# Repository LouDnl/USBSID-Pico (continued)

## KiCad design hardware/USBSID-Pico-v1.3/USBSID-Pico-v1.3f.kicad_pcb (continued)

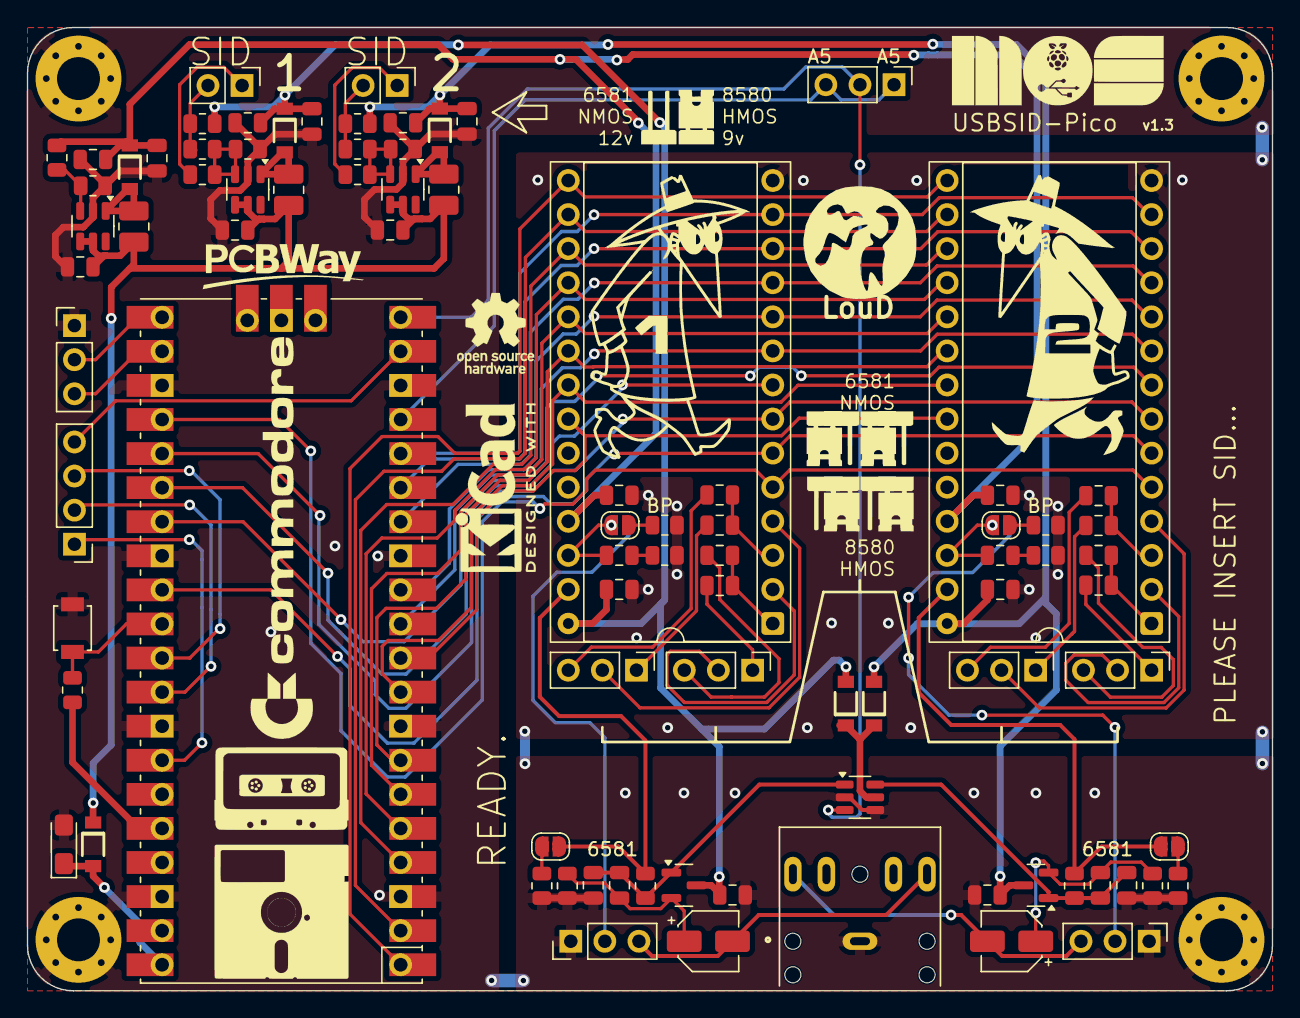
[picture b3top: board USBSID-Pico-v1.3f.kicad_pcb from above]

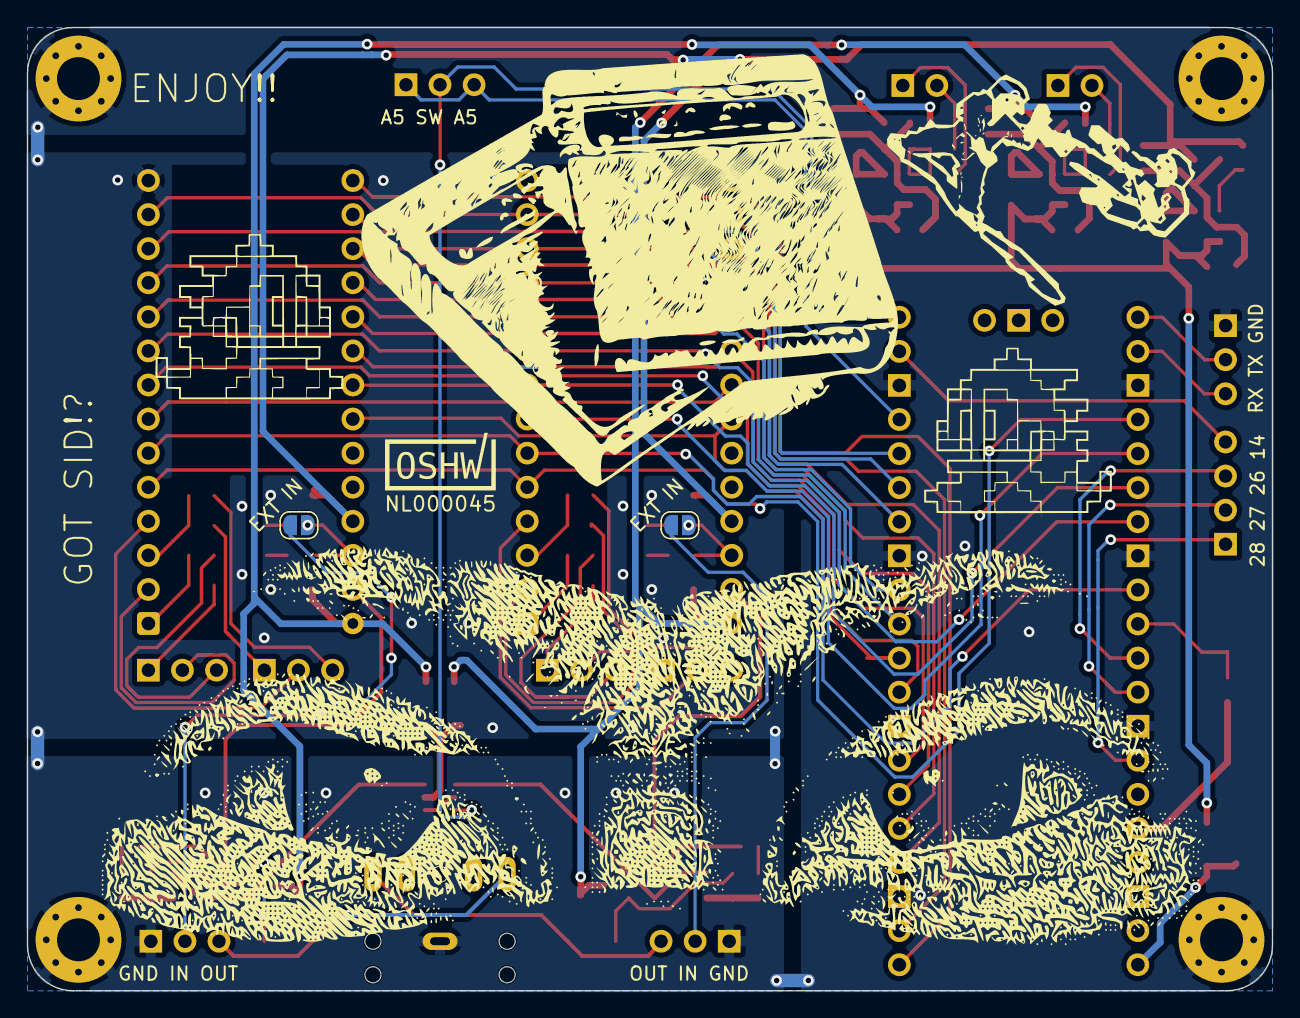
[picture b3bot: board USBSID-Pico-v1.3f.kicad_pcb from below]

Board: 2 copper layers, 92.8 x 71.8 mm, 95 parts (3 on the bottom side), 79 nets.

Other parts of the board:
NL000045: OSHW_US1.0_-Certification-Mark-Stacked_8x7mm_Silk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; OSHW_US1.0_-Certification-Mark-Stacked_8x7mm_SilkScreen

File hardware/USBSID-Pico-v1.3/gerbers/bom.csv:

Designator,Quantity,Value,Footprint,Package,MPN,DNP,Mount_Type,Description,Manufacturer,Mfg Part #,Mfg Part Desc,Mfg Qty,Sim.Device,Sim.Pins,Optional Part,Optional datasheet,Optional Part #
C1,1,10uF,CP_EIA-3216-10_Kemet-I_Pad1.58x1.35mm_HandSolder,,,,smt,T491A106(1)004A(2),KEMET,T491A106K016AT,10uF 16V 3Ω@100kHz ±10% CASE-A-3216-18(mm) Tantalum Capacitors,1,,,,,
"C10, C11",2,1000pF,C_0805_2012Metric,,,,smt,,Samsung,CL21B102KBANNNC,50V 1nF X7R ±10% 0805 Multilayer Ceramic Capacitors MLCC - SMD/SMT ROHS ,1,,,,,
"C12, C13, C2, C4, C6, C8",6,470pF,C_0805_2012Metric,,,,smt,,Guangdong Fenghua Advanced Tech,0805B471K500NT,50V 470pF X7R ±10% 0805 Multilayer Ceramic Capacitors MLCC - SMD/SMT ROHS ,1,,,,,
"C14, C15, C27, C28, C29, C30, C31, C32",8,100nF,C_0805_2012Metric,,,,smt,,Samsung,CL21B104KBCNNNC,50V 100nF X7R ±10% 0805 Multilayer Ceramic Capacitors MLCC - SMD/SMT ROHS ,1,,,,,
"C16, C17",2,10uF,CP_Elec_4x5.3,,,,smt,10UF 25V 4x5.4mm,Honor Elec,RVT1E100M0405,"10uF 25V ±20% SMD,D4xL5.4mm Aluminum Electrolytic Capacitors - SMD ROHS ",1,,,,,
"C18, C19, C20, C21, C22, C23, C24, C25, C26",9,22uF,C_0805_2012Metric,,,,smt,,Samsung,CL21A226MAQNNNE,25V 22uF X5R ±20% 0805 Multilayer Ceramic Capacitors MLCC - SMD/SMT ROHS ,1,,,,,
"C3, C5, C7, C9",4,22nF,C_0805_2012Metric,,,,smt,,Samsung,CL21B223KBANNNC,50V 22nF X7R ±10% 0805 Multilayer Ceramic Capacitors MLCC - SMD/SMT ROHS ,1,,,,,
"D1, D2, D3, D4, D5, D6",6,MBR120,SOD-123FL_diode,,,,smt,"Schottky diode, small symbol",onsemi,MBR120VLSFT1G,20V 300mV@1A 1A SOD-123FL Schottky Diodes ROHS ,1,D,1=K 2=A,,,
J1,1,SID1 (DIP28-Wide-socket),DIP-28_W15.24mm_Socket_enlargedholes,,,,tht,DIP-28_W15.24mm_Socket,CONNFLY Elec,DS1009-28AT1WX-0A2,28P DIP Tin 15.24mm 2.54mm DIP-28 IC / Transistor Socket ROHS,1,,,DIP-28 IC / Transistor Socket ROHS,https://www.lcsc.com/datasheet/lcsc_datasheet_2410121342_Han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,H2541FV-C1524-2x14P
J10,1,S2 6581/8580 J2,PinHeader_1x03_P2.54mm_Vertical,,,,tht,PinHeader_1x03_P2.54mm_Vertical,XUNPU,PH2.54-01-03PZD,"Direct Insert Policy 2.5mm 6mm 3P -40℃~+105℃ 3mm 2.54mm Black Brass Single Row 1x3P Plugin,P=2.54mm Pin Headers ROHS ",1,,,,,
J17,1,A5,PinHeader_1x03_P2.54mm_Vertical,,,Yes,tht,"Generic connector, single row, 01x03, script generated (kicad-library-utils/schlib/autogen/connector/)",XUNPU,PH2.54-01-02PZD,"Direct Insert Policy 2.5mm 6mm 2P -40℃~+105℃ 3mm 2.54mm Black Brass Single Row 1x2P Plugin,P=2.54mm Pin Headers ROHS ",1,,,,,
J18,1,UART,PinHeader_1x03_P2.54mm_Vertical,,,Yes,tht,"Generic connector, single row, 01x03, script generated (kicad-library-utils/schlib/autogen/connector/)",XUNPU,PH2.54-01-02PZD,"Direct Insert Policy 2.5mm 6mm 2P -40℃~+105℃ 3mm 2.54mm Black Brass Single Row 1x2P Plugin,P=2.54mm Pin Headers ROHS ",1,,,,,
J2,1,SID2 (DIP28-Wide-socket),DIP-28_W15.24mm_Socket_enlargedholes,,,,tht,DIP-28_W15.24mm_Socket,CONNFLY Elec,DS1009-28AT1WX-0A2,28P DIP Tin 15.24mm 2.54mm DIP-28 IC / Transistor Socket ROHS,1,,,DIP-28 IC / Transistor Socket ROHS,https://www.lcsc.com/datasheet/lcsc_datasheet_2410121342_Han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,H2541FV-C1524-2x14P
J20,1,SID1 12v/9v,PinHeader_1x02_P2.54mm_Vertical,,,,tht,"Generic connector, single row, 01x02, script generated (kicad-library-utils/schlib/autogen/connector/)",XUNPU,PH2.54-01-02PZD,"Direct Insert Policy 2.5mm 6mm 2P -40℃~+105℃ 3mm 2.54mm Black Brass Single Row 1x2P Plugin,P=2.54mm Pin Headers ROHS ",1,,,,,
J21,1,SID2 12v/9v,PinHeader_1x02_P2.54mm_Vertical,,,,tht,"Generic connector, single row, 01x02, script generated (kicad-library-utils/schlib/autogen/connector/)",XUNPU,PH2.54-01-02PZD,"Direct Insert Policy 2.5mm 6mm 2P -40℃~+105℃ 3mm 2.54mm Black Brass Single Row 1x2P Plugin,P=2.54mm Pin Headers ROHS ",1,,,,,
J24,1,OPT,PinHeader_1x04_P2.54mm_Vertical,,,Yes,tht,"Generic connector, single row, 01x04, script generated (kicad-library-utils/schlib/autogen/connector/)",XUNPU,PH2.54-01-02PZD,"Direct Insert Policy 2.5mm 6mm 2P -40℃~+105℃ 3mm 2.54mm Black Brass Single Row 1x2P Plugin,P=2.54mm Pin Headers ROHS ",1,,,,,
J3,1,S1 6581/8580 J1,PinHeader_1x03_P2.54mm_Vertical,,,,tht,PinHeader_1x03_P2.54mm_Vertical,XUNPU,PH2.54-01-03PZD,"Direct Insert Policy 2.5mm 6mm 3P -40℃~+105℃ 3mm 2.54mm Black Brass Single Row 1x3P Plugin,P=2.54mm Pin Headers ROHS ",1,,,,,
J4,1,S2 6581/8580 J1,PinHeader_1x03_P2.54mm_Vertical,,,,tht,PinHeader_1x03_P2.54mm_Vertical,XUNPU,PH2.54-01-03PZD,"Direct Insert Policy 2.5mm 6mm 3P -40℃~+105℃ 3mm 2.54mm Black Brass Single Row 1x3P Plugin,P=2.54mm Pin Headers ROHS ",1,,,,,
J6,1,GND/S1,PinHeader_1x03_P2.54mm_Vertical,,,Yes,tht,"Generic connector, single row, 01x03, script generated (kicad-library-utils/schlib/autogen/connector/)",XUNPU,PH2.54-01-02PZD,"Direct Insert Policy 2.5mm 6mm 2P -40℃~+105℃ 3mm 2.54mm Black Brass Single Row 1x2P Plugin,P=2.54mm Pin Headers ROHS ",1,,,,,
J7,1,S2/GND,PinHeader_1x03_P2.54mm_Vertical,,,Yes,tht,"Generic connector, single row, 01x03, script generated (kicad-library-utils/schlib/autogen/connector/)",XUNPU,PH2.54-01-02PZD,"Direct Insert Policy 2.5mm 6mm 2P -40℃~+105℃ 3mm 2.54mm Black Brass Single Row 1x2P Plugin,P=2.54mm Pin Headers ROHS ",1,,,,,
J8,1,SJ1-3525N,3.5MM_SWITCHCRAFT_35RAPC4BHN2,,,,tht,"Audio Jack, 2 Poles (Mono / TS), Grounded Sleeve, Switched Pole (Normalling)",CuiDevices,SJ1-3525N,Audio Jack with tip and ring switch,1,,,,https://www.lcsc.com/datasheet/lcsc_datasheet_2409272203_SHO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,PJ3F07-5P
J9,1,S1 6581/8580 J2,PinHeader_1x03_P2.54mm_Vertical,,,,tht,PinHeader_1x03_P2.54mm_Vertical,XUNPU,PH2.54-01-03PZD,"Direct Insert Policy 2.5mm 6mm 3P -40℃~+105℃ 3mm 2.54mm Black Brass Single Row 1x3P Plugin,P=2.54mm Pin Headers ROHS ",1,,,,,
"L1, L2, L3",3,"4,7uH 1000mA",L_1008_2520Metric_Pad1.43x2.20mm_HandSolder,,,,smt,"4,7uH 1000mA",SunLord,SPH252012H4R7MT,1.25A 4.7uH ±20% 1.2A 1008 Power Inductors ROHS ,1,,,,,
"Q1, Q2",2,MMBT2222A,SOT-23,,,,smt,"15A Ic, 60V Vce, Power NPN Transistor, TO-3",onsemi,MMBT2222ALT1G,"40V 225mW 100@150mA,10V 600mA NPN SOT-23 Bipolar (BJT) ROHS ",1,,,,,
"R1, R2, R4",3,10k,R_0805_2012Metric,,,,smt,"Resistor, small symbol",UNI-ROYAL,0805W8F1002T5E,125mW Thick Film Resistors 150V ±100ppm/℃ ±1% 10kΩ 0805 Chip Resistor - Surface Mount ROHS ,1,,,,,
"R10, R16, R17, R3, R5, R6, R7, R8, R9",9,1k,R_0805_2012Metric,,,,smt,,"[R8,R9]UNI-ROYAL; [R5,R6,R7]UNI-ROYAL ",0805W8F1001T5E,"[R8,R9]125mW Thick Film Resistors 150V ±100ppm/℃ ±1% 1kΩ 0805 Chip Resistor - Surface Mount ROHS ; [R3,R5,R6,R7]125mW Thick Film Resistors 150V ±100ppm/℃ ±1% 1kΩ 0805 Chip Resistor - Surface Mount ROHS  ",1,,,,,
R11,1,"7,5k",R_0805_2012Metric,,,,smt,,UNI-ROYAL,0805W8F7501T5E,125mW Thick Film Resistors 150V ±100ppm/℃ ±1% 7.5kΩ 0805 Chip Resistor - Surface Mount ROHS ,1,,,,,
"R12, R14",2,18k,R_0805_2012Metric,,,,smt,,UNI-ROYAL,0805W8F1802T5E,125mW Thick Film Resistors 150V ±100ppm/℃ ±1% 18kΩ 0805 Chip Resistor - Surface Mount ROHS ,1,,,,,
"R13, R15",2,47k,R_0805_2012Metric,,,,smt,,UNI-ROYAL,0805W8F4702T5E,125mW Thick Film Resistors 150V ±100ppm/℃ ±1% 47kΩ 0805 Chip Resistor - Surface Mount ROHS ,1,,,,,
"R18, R19",2,330k,R_0805_2012Metric,,,,smt,,UNI-ROYAL,0805W8F3303T5E,125mW Thick Film Resistors 150V ±100ppm/℃ ±1% 330kΩ 0805 Chip Resistor - Surface Mount ROHS ,1,,,,,
"R20, R21",2,100k,R_0805_2012Metric,,,,smt,,UNI-ROYAL,0805W8F1003T5E,125mW Thick Film Resistors 150V ±100ppm/℃ ±1% 100kΩ 0805 Chip Resistor - Surface Mount ROHS ,1,,,,,
SW1,1,RST,SW_SPST_B3U-1000P_larger_pads,,,,smt,"Push button switch, generic, two pins",Omron Electronics ,B3U-1000P,"2.5mm 1.6mm Round Button 50mA Standing paste 3mm SPST 153gf 12V SMD,2.5x3mm Tactile Switches ROHS ",1,,,,,
"U2, U3, U4",3,MT3608,SOT-23-6,,,,smt,,AeroSemi,MT3608,High Efficiency 1.2MHz 2A Step Up Converter,1,,,,,
U5,1,DG467,SOT-23-6,,,,smt,"Low Power, High Voltage SPST Analog Switches, 6-Pin TSOP",Vishay,DG467DV-T1-E3,"Low Power, High Voltage SPST Analog Switches",1,,,,,

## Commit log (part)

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2026-02-28 Fix storage size, move around some boxes
2026-02-28 Static electricity
2026-02-28 One must always return when static electricity hits!
2026-02-28 Remove unneeded macro use
2026-02-28 Bzzz.. more statics!
2026-02-28 [BREAKING CHANGE] Rewrite configuration logic, improve and clear up logging and update sid / chip detections. Add limited ARMSID, PDSID & BACKSID support.
2026-02-28 Really, 3 characters and everything breaks 👻
2026-02-28 Tag, you're it! 😈
2026-02-28 Riff raffs
2026-02-28 First iteration update CLI config-tool
2026-03-01 Config-tool update
2026-03-01 Moar updates!
2026-03-01 Remove pre-compiled tool binaries from source code
2026-03-02 I can't count
2026-03-03 Emu here, emu there, emu everywhere
2026-03-03 Let's not forget
2026-03-04 Off with their heads! I mean headers!
2026-03-04 Spring cleaning! No more externs, let's internalise in our head(ers) 👾
2026-03-04 Add moar 🧌 presets!
2026-03-04 Hey Ren? Yes Stimpy? Are whe there yet!?
2026-03-04 Almost Stimpy, almost!!
2026-03-04 Spilled my drink there
2026-03-04 All hail the FPGASID
2026-03-04 Fixle Smixzle
2026-03-04 Add optional play on on socket two for embedded player
2026-03-04 Update `send_sid` for optional play on on socket two
2026-03-07 Move webconfig tool into old directory
2026-03-08 Save copy of current webconfig tool in new directory
2026-03-08 .gitignore
2026-03-08 First iteration of new webconfig tool
2026-03-08 Fix RGBLED selection always falling back to SID 1
2026-03-08 Logging shmogging
2026-03-08 Fix arm2sid detection
2026-03-08 Add read armsid configuration
2026-03-08 Docstringz
2026-03-08 webconfig tool updates
2026-03-08 And some more :)
2026-03-08 Add notice
2026-03-08 Change config read number of packets
2026-03-08 Update some test functions
2026-03-08 Switch out vendor writes for vendor N writes as test
2026-03-13 Testing testing one two three...
2026-03-13 Me no pay!
2026-03-15 Add Cynthcart VST by Raros
2026-04-28 Just encase it!
2026-04-28 Add SIDEmu detection
2026-04-28 add SIDEmu string and 2 bugs squashed :)
2026-04-28 missing dtypes.. 🍆
2026-04-28 Add missing `CHIP_SIDEMU` thingy and prepare for socket change detection
2026-04-28 Fix for SIDEmu
2026-04-28 Midi rework continued
2026-05-16 Enable direct midi access even in onboard emulator is present
2026-05-16 Change midi->SID control to user defined channel and save settings per channel (like an instrument)
2026-05-17 Rename midi_cc to midi_defs
2026-05-17 Moar defzz!
2026-05-26 Deprecate usbsid_doubletap
2026-05-30 Bright light, bright light! 🕶️
2026-05-30 Handyman candyman debug sorting
2026-05-30 DMA soothing 🍼
2026-05-30 What isn't known shall not be seen
2026-05-30 You put something in, you take something out, it goes boom!
2026-05-30 Clean up the mess you make!
2026-05-30 Something, power, something
2026-05-30 General purpose who!? More like Corporal?
2026-05-30 Macro, sounds like Macaroni! 🍝
2026-05-30 Piiiioooo, Piiiooo, what?
2026-05-30 Undetected 🕵️
2026-05-30 That's a whole lot of detecting officer!
2026-05-30 Cleanup on aisle 4!
2026-05-30 Constant here, constant there, trying to be constant everywhere
2026-05-30 That's a lot of stuff to change!
2026-05-30 Wow... no words
2026-05-30 Loop de loop updates
2026-05-30 I taught I saw a puttycat
2026-05-30 There can only be one tool to rule them all!
2026-05-30 Dust off the 'ol buildscript
2026-06-13 Add support for v1.5, fix incorrect packet length on reads (must be 64 bytes for webusb), clean up
2026-06-13 Fix fat fingers
2026-06-13 Debug logging for later alligator
2026-06-13 Disable uart spam on preset applying
2026-06-13 cleanup
2026-06-13 Fix voltage set order for v1.5 boards so clone sids don't phreak out!
2026-06-13 Roundabout
2026-06-13 Add stdio_flush during pio bus setup and sync, would mess up memory otherwise
2026-06-13 House cleaning
2026-06-13 Config improvements, also some v1.5 additions/fixes
2026-06-13 Fix branch detection, some cleanup
2026-06-13 Add workaround for lingering data in the vendor fifo
2026-06-13 Prepare for bluetooth
2026-06-13 Fix order in detect_chiptype_at
2026-06-13 Fix fallback in verify_socket_chip
2026-06-13 Update CC's
2026-06-13 Direct Midi control update (not finished yet)
2026-06-13 Add initial v1.5 information, reference configtool
2026-06-14 Documentation update
2026-06-21 Add breaks in preparation of Chip config
2026-06-21 Update log message
2026-06-21 Remove todo
2026-06-21 Readability
2026-06-21 Add GET_AUDIO config command
2026-06-21 Swap out inline write backs for wrapper function
2026-06-21 Init READ/WRITE CLONECHIP commands
2026-06-21 Fix test logging
2026-06-21 Add required config commands to header
2026-06-21 Enforce stdio_flush after each uart log write
2026-06-21 Init read/write chipconfig
2026-06-21 test logging after config command reading
2026-06-21 formatting
2026-06-21 Bump version
2026-06-28 Update gitlab CI
2026-06-28 Fix race conditions in build pipeline
2026-06-28 Fix build errors due to incorrect toolchain use
2026-06-28 Consolidate build pipelines into a single runner
2026-06-28 Enable Windows and MacOS ARM in gitlab CI on gitlab.com only
